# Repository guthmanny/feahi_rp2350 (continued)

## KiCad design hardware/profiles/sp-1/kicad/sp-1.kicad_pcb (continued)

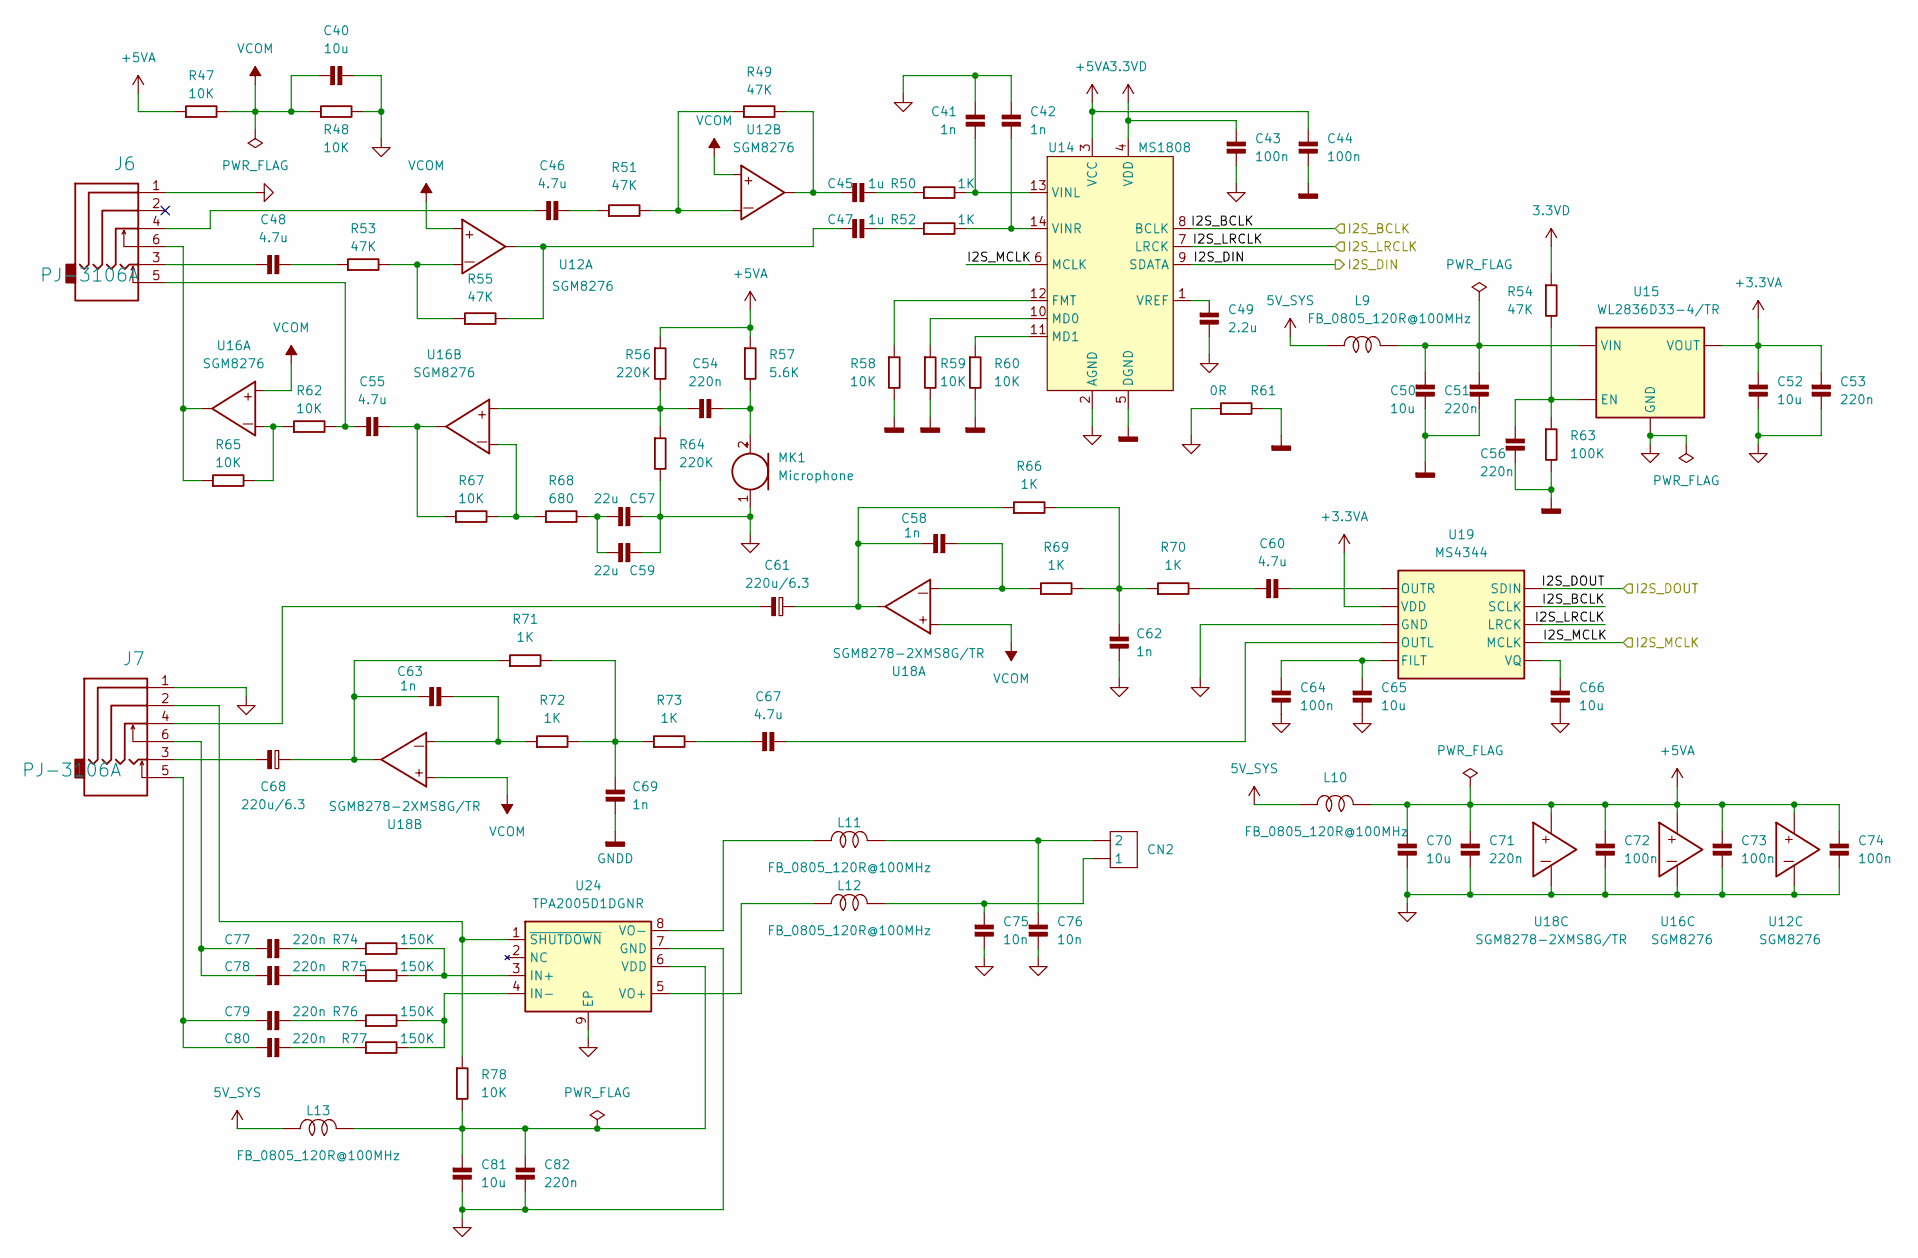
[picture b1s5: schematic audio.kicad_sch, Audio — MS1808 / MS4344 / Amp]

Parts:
C40, C50, C52, C65, C66, C70, C81: 10u; C_0603_1608Metric_Pad1.08x0.95mm_HandSolder
C41, C42, C58, C62, C63, C69: 1n; C_0402_1005Metric_Pad0.74x0.62mm_HandSolder
C43, C44, C64, C72, C73, C74: 100n; C_0402_1005Metric_Pad0.74x0.62mm_HandSolder
C45, C47: 1u; C_0603_1608Metric_Pad1.08x0.95mm_HandSolder
C46, C48, C55, C60, C67: 4.7u; C_0603_1608Metric_Pad1.08x0.95mm_HandSolder
C49: 2.2u; C_0402_1005Metric_Pad0.74x0.62mm_HandSolder
C51, C53, C54, C56, C71, C82: 220n; C_0603_1608Metric_Pad1.08x0.95mm_HandSolder
C57, C59: 22u; C_0603_1608Metric_Pad1.08x0.95mm_HandSolder
C61, C68: 220u/6.3; CP_Elec_6.3x5.4
C75, C76: 10n; C_0402_1005Metric_Pad0.74x0.62mm_HandSolder
C77, C78, C79, C80: 220n; C_0402_1005Metric_Pad0.74x0.62mm_HandSolder
CN2: Connector 1*2_2.0; 2PIN - 2.0
J6, J7: PJ-3106A; PJ3106A
L9, L10, L11, L12, L13: FB_0805_120R@100MHz; L_0805_2012Metric_Pad1.05x1.20mm_HandSolder
MK1: Microphone; 2PIN - 2.0
R47, R48, R58, R59, R60, R62, R65, R67, R78: 10K; R_0402_1005Metric_Pad0.72x0.64mm_HandSolder
R49, R51, R53, R54, R55: 47K; R_0402_1005Metric_Pad0.72x0.64mm_HandSolder
R50, R52, R66, R69, R70, R71, R72, R73: 1K; R_0402_1005Metric_Pad0.72x0.64mm_HandSolder
R56, R64: 220K; R_0603_1608Metric_Pad0.98x0.95mm_HandSolder
R57: 5.6K; R_0402_1005Metric_Pad0.72x0.64mm_HandSolder
R61: 0R; R_0603_1608Metric_Pad0.98x0.95mm_HandSolder
R63: 100K; R_0402_1005Metric_Pad0.72x0.64mm_HandSolder
R68: 680; R_0402_1005Metric_Pad0.72x0.64mm_HandSolder
R74, R75, R76, R77: 150K; R_0402_1005Metric_Pad0.72x0.64mm_HandSolder
U12, U16: SGM8276; SOP-8
U14: MS1808; TSSOP14; Part Number MS1808
U15: WL2836D33-4/TR; DFN1x1-4L
U18: SGM8278-2XMS8G/TR; MSOP-8; Part Number SGM5532YS8G/TR
U19: MS4344; MSOP-10
U24: TPA2005D1DGNR; Texas_DGN0008D_VSSOP-8-1EP_3x3mm_P0.65mm_EP2x2.94mm_Mask1.5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

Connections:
3.3VD: C43.1, R54.1, U14.4 (VDD); also elsewhere on the board
5V_SYS: L9.1, L10.1, L13.1; also elsewhere on the board
+3.3VA: C52.1, C53.1, U15.1 (VOUT), U19.9 (VDD)
+5VA: C44.1, C70.1, C71.1, C72.1, C73.1, C74.1, L10.2, R47.1, R56.1, R57.1, U12.8, U14.3 (VCC), U16.8, U18.8
/audio/I2S_BCLK: U14.8 (BCLK), U19.2 (SCLK); also elsewhere on the board
/audio/I2S_DIN: U14.9 (SDATA); also elsewhere on the board
/audio/I2S_DOUT: U19.1 (SDIN); also elsewhere on the board
/audio/I2S_LRCLK: U14.7 (LRCK), U19.3 (LRCK); also elsewhere on the board
/audio/I2S_MCLK: U14.6 (MCLK), U19.4 (MCLK); also elsewhere on the board
GNDA: C40.2, C41.2, C42.2, C43.2, C49.2, C52.2, C53.2, C57.2, C59.2, C62.2, C64.2, C65.2, C66.2, C70.2, C71.2, C72.2, C73.2, C74.2, C75.2, C76.2, C81.2, C82.2, J6.1, J7.1, MK1.1 (-), R48.2, R61.1, R64.2, U12.4, U14.2 (AGND), U15.2 (GND), U15.5 (GNDA), U16.4, U18.4, U19.8 (GND), U24.7 (GND), U24.9 (EP)
GNDD: C44.2, C50.2, C51.2, C56.2, C69.2, R58.2, R59.2, R60.2, R61.2, R63.2, U14.5 (DGND); also elsewhere on the board
unnamed: C45.1, R50.1
unnamed: C45.2, R49.2, U12.7
unnamed: C46.1, J6.4
unnamed: C46.2, R51.1
unnamed: C47.1, R52.1
unnamed: C47.2, R55.2, U12.1
unnamed: C48.1, J6.3
unnamed: C48.2, R53.1
unnamed: C54.1, R56.2, R64.1, U16.5
unnamed: C55.1, J6.5, R62.2
unnamed: C55.2, R67.1, U16.7
unnamed: C57.1, C59.1, R68.2
unnamed: C58.1, C61.1, R66.1, U18.1
unnamed: C58.2, R69.1, U18.2
unnamed: C60.1, R70.2
unnamed: C61.2, J7.4
unnamed: C62.1, R66.2, R69.2, R70.1
unnamed: C63.1, C68.1, R71.1, U18.7
unnamed: C63.2, R72.1, U18.6
unnamed: C67.1, R73.2
unnamed: C68.2, J7.3
unnamed: C69.1, R71.2, R72.2, R73.1
unnamed: C75.1, CN2.1, L12.2
unnamed: C76.1, CN2.2, L11.2
unnamed: C77.1, C78.1, J7.6
unnamed: C77.2, R74.1
unnamed: C78.2, R75.1
unnamed: C79.1, C80.1, J7.5
unnamed: C79.2, R76.1
unnamed: C80.2, R77.1
unnamed: J6.6, R65.1, U16.1
unnamed: C54.2, MK1.2 (+), R57.2
unnamed: R49.1, R51.2, U12.6
unnamed: R53.2, R55.1, U12.2
unnamed: R62.1, R65.2, U16.2
unnamed: R67.2, R68.1, U16.6
unnamed: R58.1, U14.12 (FMT)
unnamed: R59.1, U14.10 (MD0)
unnamed: R60.1, U14.11 (MD1)
unnamed: C41.1, R50.2, U14.13 (VINL)
unnamed: C42.1, R52.2, U14.14 (VINR)
unnamed: C49.1, U14.1 (VREF)
unnamed: C56.1, R54.2, R63.1, U15.3 (EN)
unnamed: C50.1, C51.1, L9.2, U15.4 (VIN)
unnamed: C64.1, C65.1, U19.6 (FILT)
unnamed: C67.2, U19.7 (OUTL)
unnamed: C60.2, U19.10 (OUTR)
unnamed: C66.1, U19.5 (VQ)
unnamed: R74.2, R75.2, U24.3 (IN+)
unnamed: R76.2, R77.2, U24.4 (IN-)
unnamed: C81.1, C82.1, L13.2, R78.2, U24.6 (VDD)
unnamed: L12.1, U24.5 (VO+)
unnamed: L11.1, U24.8 (VO-)
unnamed: J7.2, R78.1, U24.1 (~SHUTDOWN)
VCOM: C40.1, R47.2, R48.1, U12.3, U12.5, U16.3, U18.3, U18.5

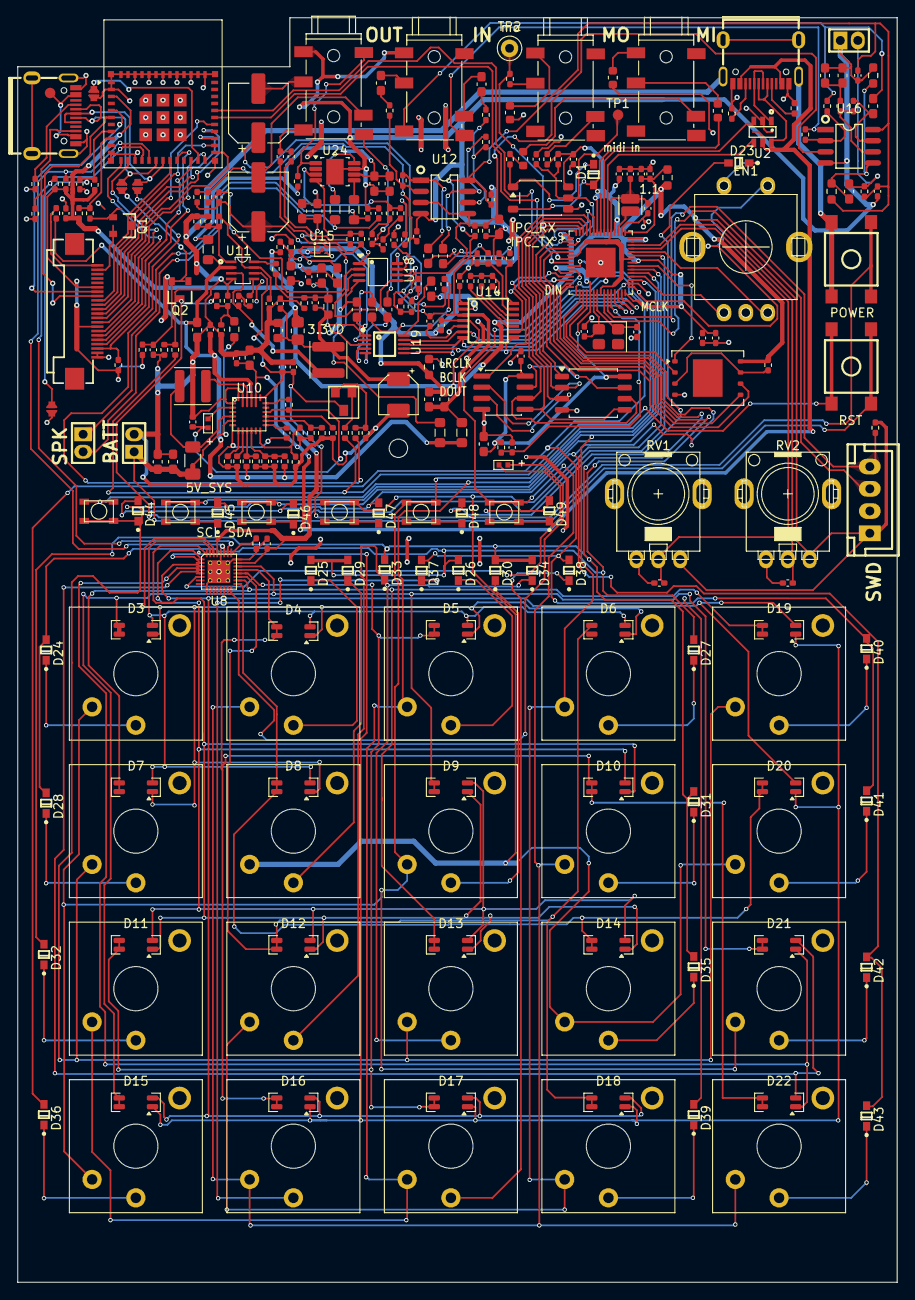
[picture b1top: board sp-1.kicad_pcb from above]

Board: 2 copper layers, 100.5 x 144.5 mm, 295 parts (0 on the bottom side), 220 nets.

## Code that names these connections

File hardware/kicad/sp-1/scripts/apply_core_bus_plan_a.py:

#!/usr/bin/env python3
"""Plan A: QMI bus_alias + {QMI} label; FLASH_CS off bus (core.kicad_sch)."""
from __future__ import annotations

import re
import uuid
from pathlib import Path

CORE = Path(__file__).resolve().parent.parent / "core.kicad_sch"

BUS_ALIAS_BLOCK = """\t(bus_alias "QMI"
\t\t(members "QSPI_SCLK" "QSPI_SD0" "QSPI_SD1" "QSPI_SD2" "QSPI_SD3")
\t)
"""

# Horizontal QMI trunk in current core layout (KiCad grid 2.54 mm).
BUS_H_Y = 88.9
BUS_H_X0 = 85.09
BUS_H_X1 = 120.65
BUS_LABEL_X = (BUS_H_X0 + BUS_H_X1) / 2.0

BUS_LABEL = """\t(label "{{QMI}}"
\t\t(at {x:.4f} {y:.4f} 0)
\t\t(effects
\t\t\t(font
\t\t\t\t(size 1.27 1.27)
\t\t\t)
\t\t\t(justify left bottom)
\t\t)
\t\t(uuid "{uuid}")
\t)"""

CS_BUS_ENTRIES = frozenset({(84.836, 94.488), (84.836, 97.028), (121.158, 93.726)})

CS_WIRE_UUIDS = frozenset(
    {
        "24ad6d66-7ffd-4be0-8b8e-321d4a02af30",
        "90382c6a-58d1-40ab-a2b1-7a4dca7b072f",
    }
)

BUS_ENTRY_BLOCK = re.compile(
    r"\t\(bus_entry\n"
    r"\t\t\(at (?P<x>[-0-9.]+) (?P<y>[-0-9.]+)\)\n"
    r"\t\t\(size [^\n]+\n"
    r"\t\t\(stroke\n"
    r"\t\t\t\(width 0\)\n"
    r"\t\t\t\(type default\)\n"
    r"\t\t\)\n"
    r"\t\t\(uuid \"[a-f0-9-]+\"\)\n"
    r"\t\)\n",
    re.MULTILINE,
)

WIRE_BLOCK = re.compile(
    r"\t\(wire\n"
    r"(?:.*?\n)*?"
    r"\t\t\(uuid \"(?P<u>[a-f0-9-]+)\"\)\n"
    r"\t\)\n",
    re.MULTILINE,
)

LABEL_FLASH = re.compile(
    r"\t\(label \"FLASH_CS\"\n"
    r"\t\t\(at (?P<x>[-0-9.]+) (?P<y>[-0-9.]+)[^\n]*\n"
    r"(?:.*?\n)*?"
    r"\t\t\(uuid \"[a-f0-9-]+\"\)\n"
    r"\t\)\n",
    re.MULTILINE,
)


def uid() -> str:
    return str(uuid.uuid4())


def flash_cs_wires() -> str:
    return f"""\t(wire
\t\t(pts
\t\t\t(xy 72.3900 97.0280) (xy 128.0000 97.0280)
\t\t)
\t\t(stroke
\t\t\t(width 0)
\t\t\t(type default)
\t\t)
\t\t(uuid "{uid()}")
\t)
\t(wire
\t\t(pts
\t\t\t(xy 128.0000 97.0280) (xy 128.0000 93.7260)
\t\t)
\t\t(stroke
\t\t\t(width 0)
\t\t\t(type default)
\t\t)
\t\t(uuid "{uid()}")
\t)
\t(wire
\t\t(pts
\t\t\t(xy 128.0000 93.7260) (xy 133.6040 93.7260)
\t\t)
\t\t(stroke
\t\t\t(width 0)
\t\t\t(type default)
\t\t)
\t\t(uuid "{uid()}")
\t)
\t(label "FLASH_CS"
\t\t(at 100.0000 97.0280 0)
\t\t(effects
\t\t\t(font
\t\t\t\t(size 1.27 1.27)
\t\t\t)
\t\t\t(justify left bottom)
\t\t)
\t\t(uuid "{uid()}")
\t)"""


def add_bus_alias(text: str) -> str:
    if '(bus_alias "QMI"' in text:
        return text
    anchor = "\t(embedded_fonts no)\n\t\t)\n\t)\n"
    idx = text.find(anchor)
    if idx < 0:
        raise SystemExit("lib_symbols end not found.")
    insert_at = idx + len(anchor)
    return text[:insert_at] + BUS_ALIAS_BLOCK + text[insert_at:]


def ensure_bus_label(text: str) -> str:
    lbl = BUS_LABEL.format(x=BUS_LABEL_X, y=BUS_H_Y, uuid=uid())
    if '(label "{QMI}"' in text:
        text = re.sub(
            r'\(label "\{QMI\}"\n\t\t\(at [^\n]+\n',
            f'(label "{{QMI}}"\n\t\t(at {BUS_LABEL_X:.4f} {BUS_H_Y:.4f} 0)\n',
            text,
            count=1,
        )
        return text
    # Replace legacy inline group label if present.
    text = re.sub(
        r'\t\(label "\{QSPI_SCLK QSPI_SD0 QSPI_SD1 QSPI_SD2 QSPI_SD3\}"\n'
        r"\t\t\(at [^\n]+\n"
        r"\t\t\(effects\n"
        r"\t\t\t\(font\n"
        r"\t\t\t\t\(size 1\.27 1\.27\)\n"
        r"\t\t\t\)\n"
        r"\t\t\t\(justify left bottom\)\n"
        r"\t\t\)\n"
        r'\t\t\(uuid "[a-f0-9-]+"\)\n'
        r"\t\)\n",
        lbl + "\n",
        text,
        count=1,
    )
    if '(label "{QMI}"' not in text:
        m = re.search(
            rf"(\t\(bus\n\t\t\(pts\n\t\t\t\(xy {BUS_H_X0:g} {BUS_H_Y:g}\) \(xy {BUS_H_X1:g} {BUS_H_Y:g}\)\n"
            r"\t\t\)\n\t\t\(stroke\n\t\t\t\(width 0\)\n\t\t\t\(type default\)\n"
            r"\t\t\)\n\t\t\(uuid \"[a-f0-9-]+\"\)\n\t\)\n)",
            text,
        )
        if not m:
            raise SystemExit("Horizontal QMI bus not found.")
        text = text[: m.end()] + "\n" + lbl + "\n" + text[m.end() :]
    return text


def remove_all_bus_entries(text: str) -> str:
    """Bus entries are optional; removing them avoids 'wire not at entry' ERC."""
    return BUS_ENTRY_BLOCK.sub("", text)


def remove_cs_bus_entries(text: str) -> str:
    def repl(m: re.Match[str]) -> str:
        x, y = float(m.group("x")), float(m.group("y"))
        for cx, cy in CS_BUS_ENTRIES:
            if abs(x - cx) < 0.001 and abs(y - cy) < 0.001:
                return ""
        return m.group(0)

    return BUS_ENTRY_BLOCK.sub(repl, text)


def extend_left_bus_for_u8_sclk(text: str) -> str:
    return text.replace(
        f"(xy {BUS_H_X0:g} 68.58) (xy {BUS_H_X0:g} {BUS_H_Y:g})",
        f"(xy {BUS_H_X0:g} 66.04) (xy {BUS_H_X0:g} {BUS_H_Y:g})",
        1,
    )


def remove_cs_wires(text: str) -> str:
    def repl(m: re.Match[str]) -> str:
        return "" if m.group("u") in CS_WIRE_UUIDS else m.group(0)

    return WIRE_BLOCK.sub(repl, text)


def remove_cs_stub_labels(text: str) -> str:
    def repl(m: re.Match[str]) -> str:
        x, y = float(m.group("x")), float(m.group("y"))
        if (abs(x - 82.296) < 0.001 and abs(y - 97.028) < 0.001) or (
            abs(x - 123.698) < 0.001 and abs(y - 93.726) < 0.001
        ):
            return ""
        return m.group(0)

    return LABEL_FLASH.sub(repl, text)


def trim_right_bus(text: str) -> str:
    seg = re.compile(
        r"\t\(bus\n"
        r"\t\t\(pts\n"
        r"\t\t\t\(xy 121\.158 88\.9\) \(xy 121\.158 93\.726\)\n"
        r"\t\t\)\n"
        r"\t\t\(stroke\n"
        r"\t\t\t\(width 0\)\n"
        r"\t\t\t\(type default\)\n"
        r"\t\t\)\n"
        r"\t\t\(uuid \"[a-f0-9-]+\"\)\n"
        r"\t\)\n",
        re.MULTILINE,
    )
    text, _ = seg.subn("", text, count=1)
    return text.replace(
        "(xy 121.158 93.726) (xy 121.158 98.806)",
        "(xy 121.158 96.266) (xy 121.158 98.806)",
        1,
    )


def add_flash_cs_route(text: str) -> str:
    if "128.0000 97.0280" in text:
        return text
    m = re.search(r"\n\t\(label \"PSRAM_CS\"", text)
    if not m:
        raise SystemExit("Insert point for FLASH_CS not found.")
    return text[: m.start()] + "\n" + flash_cs_wires() + text[m.start() :]


def main() -> None:
    text = CORE.read_text(encoding="utf-8")
    text = add_bus_alias(text)
    text = ensure_bus_label(text)
    text = remove_cs_bus_entries(text)
    text = trim_right_bus(text)
    text = remove_cs_wires(text)
    text = remove_cs_stub_labels(text)
    text = add_flash_cs_route(text)
    text = extend_left_bus_for_u8_sclk(text)
    text = remove_all_bus_entries(text)
    CORE.write_text(text, encoding="utf-8")
    print(f"Applied Plan A to {CORE}")


if __name__ == "__main__":
    main()

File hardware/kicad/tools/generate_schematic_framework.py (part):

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            U1  ESP32-C6-MINI-1 (4MB flash)
            GPIO map: hardware/schematic/c6_gpio.csv

            IPC UART0: GPIO16 TX / GPIO17 RX
            I2C: GPIO6/7 → UI sheet
            8080 LCD: see periph_lcd sheet
            """
        ),
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            U-KB   TCA8418 I2C keypad (0x34)
            U-LED  IS31FL3733 I2C LED (0x55)
            SW     Matrix pads + PWR via TCA
            ENC    Quadrature → C6 GPIO12/13/8

            All I2C board-only (not on CBI)
            """
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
